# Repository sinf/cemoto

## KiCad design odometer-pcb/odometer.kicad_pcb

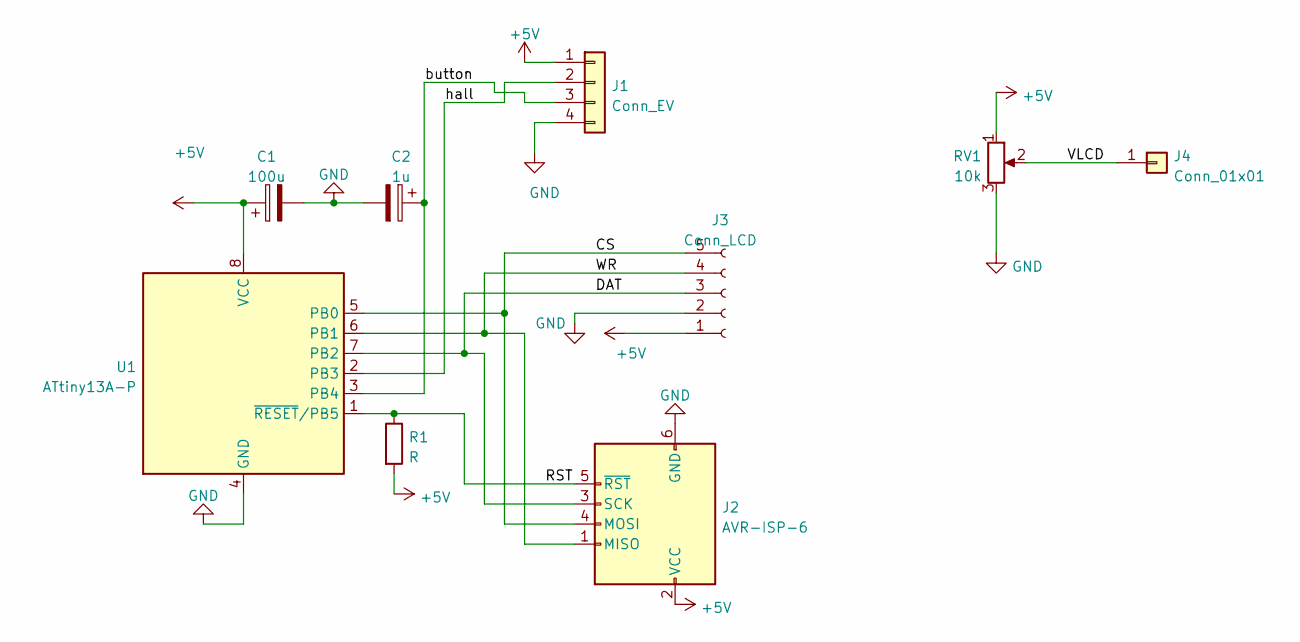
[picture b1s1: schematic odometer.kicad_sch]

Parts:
C1: 100u; CP_Radial_D8.0mm_P5.00mm
C2: 1u; CP_EIA-3216-12_Kemet-S
J1: Conn_EV; PinHeader_1x04_P2.54mm_Vertical
J2: AVR-ISP-6; PinHeader_2x03_P2.54mm_Vertical_SMD
J3: Conn_LCD; PinHeader_1x05_P2.54mm_Vertical
J4: Conn_01x01; PinHeader_1x01_P2.54mm_Vertical
R1: R; R_1206_3216Metric_Pad1.30x1.75mm_HandSolder
RV1: 10k; Potentiometer_ACP_CA9-H5_Horizontal
U1: ATtiny13A-P; DIP-8_W7.62mm

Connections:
+5V: C1.1, J1.1, J2.2 (VCC), J3.1, R1.2, RV1.1, U1.8 (VCC)
/CS: J2.4 (MOSI), J3.5, U1.5 (PB0)
/DAT: J2.3 (SCK), J3.3, U1.7 (PB2)
/RST: J2.5 (~RST), R1.1, U1.1 (~RESET/PB5)
/VLCD: J4.1, RV1.2
/WR: J2.1 (MISO), J3.4, U1.6 (PB1)
/button: C2.1, J1.3, U1.3 (PB4)
/hall: J1.2, U1.2 (PB3)
GND: C1.2, C2.2, J1.4, J2.6 (GND), J3.2, RV1.3, U1.4 (GND)

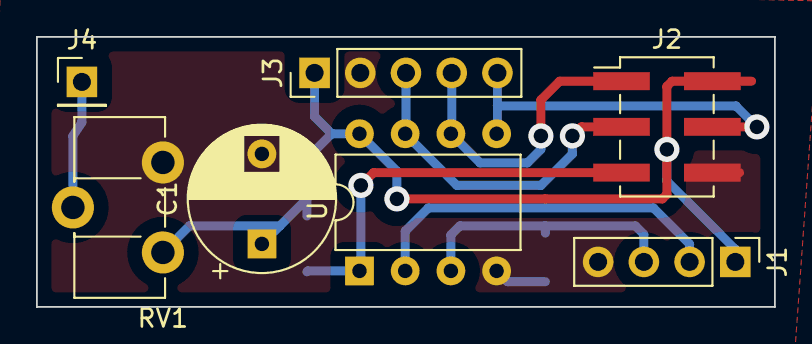
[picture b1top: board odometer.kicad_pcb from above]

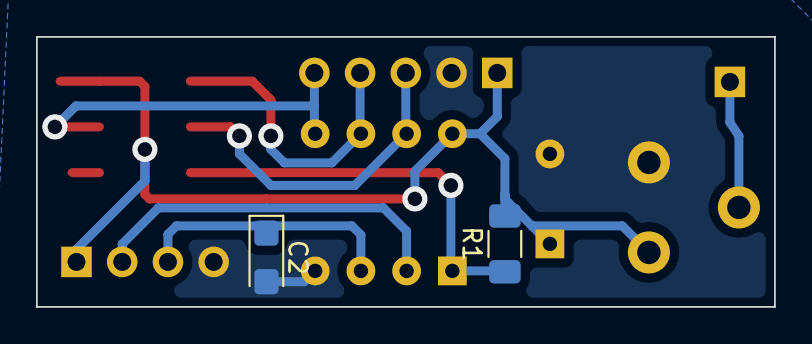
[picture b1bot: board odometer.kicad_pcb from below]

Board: 2 copper layers, 41.0 x 15.0 mm, 9 parts (2 on the bottom side), 9 nets.

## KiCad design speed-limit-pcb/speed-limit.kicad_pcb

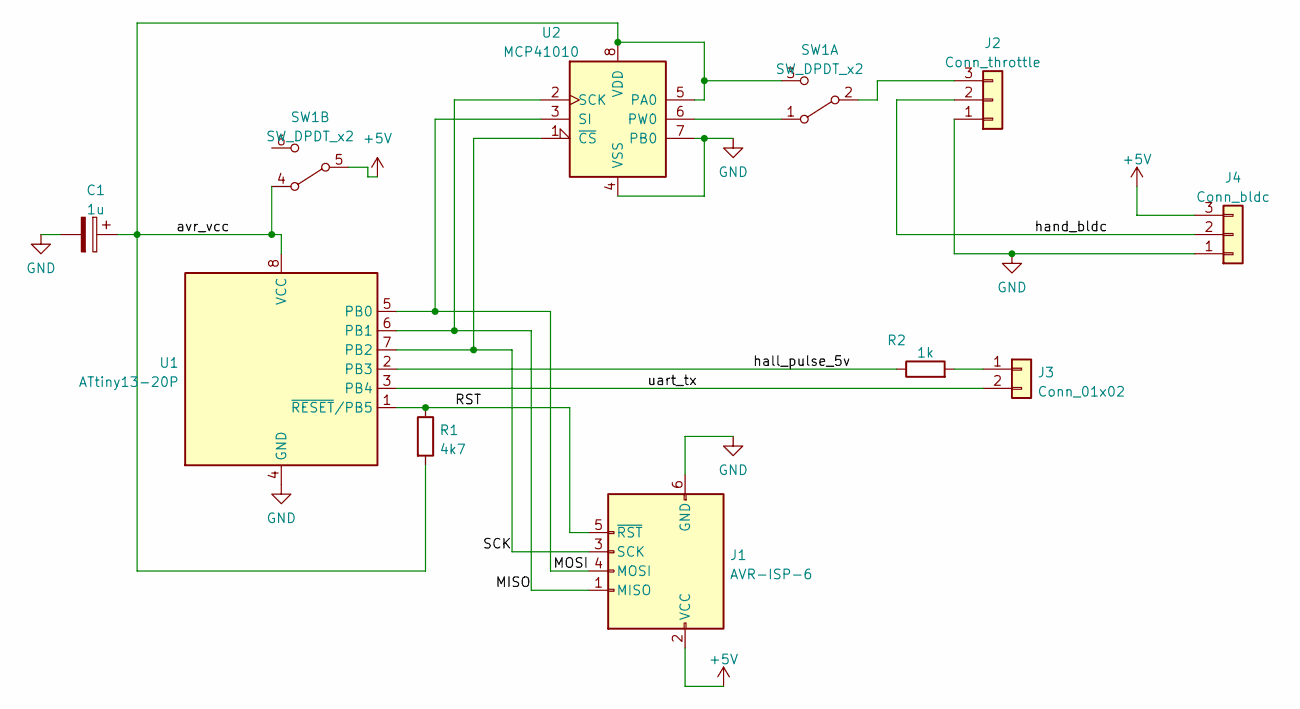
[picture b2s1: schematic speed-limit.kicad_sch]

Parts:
C1: 1u; CP_Radial_D8.0mm_P5.00mm
J1: AVR-ISP-6; SW_DIP_SPSTx03_Slide_9.78x9.8mm_W8.61mm_P2.54mm
J2: Conn_throttle; SolderWire-1.5sqmm_1x03_P6mm_D1.7mm_OD3mm
J3: Conn_01x02; SolderWire-1.5sqmm_1x02_P6mm_D1.7mm_OD3mm
J4: Conn_bldc; SolderWire-1.5sqmm_1x03_P6mm_D1.7mm_OD3mm
R1: 4k7; R_1210_3225Metric_Pad1.30x2.65mm_HandSolder
R2: 1k; R_1210_3225Metric_Pad1.30x2.65mm_HandSolder
SW1: SW_DPDT_x2; SolderWire-1.5sqmm_1x06_P6mm_D1.7mm_OD3mm
U1: ATtiny13-20P; DIP-8_W7.62mm_Socket_LongPads
U2: MCP41010; DIP-8_W7.62mm_Socket_LongPads

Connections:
+5V: J1.2 (VCC), J4.3, SW1.5 (B)
/MISO: J1.1 (MISO), U1.6 (PB1), U2.2 (SCK)
/MOSI: J1.4 (MOSI), U1.5 (PB0), U2.3 (SI)
/RST: J1.5 (~RST), R1.1, U1.1 (~RESET/PB5)
/SCK: J1.3 (SCK), U1.7 (PB2), U2.1 (~CS)
/avr_vcc: C1.1, R1.2, SW1.3 (C), SW1.4 (A), U1.8 (VCC), U2.5 (PA0), U2.8 (VDD)
/hall_pulse_5v: R2.1, U1.2 (PB3)
/hand_bldc: J2.2, J4.2
/uart_tx: J3.2, U1.3 (PB4)
GND: C1.2, J1.6 (GND), J2.1, J4.1, U1.4 (GND), U2.4 (VSS), U2.7 (PB0)
unnamed: J2.3, SW1.2 (B)
unnamed: J3.1, R2.2
unnamed: SW1.1 (A), U2.6 (PW0)

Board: 2 copper layers, 10 parts (0 on the bottom side), 13 nets, no tracks yet.

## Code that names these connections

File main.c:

#ifndef F_CPU
#define F_CPU 9600000UL
#endif

#include <stdint.h>
#include <stdlib.h>
#include <string.h>
#include <math.h>
#include <avr/io.h>
#include <avr/interrupt.h>
#include <util/delay.h>
#include <util/delay_basic.h>

// digital potentiometer pins
// max spi freq = 10 MHz
#define SDI (1u<<0)
#define SCK (1u<<1)
#define CS (1u<<2)
#define spi_delay() _delay_loop_1(10)
#define spi_delay2() _delay_loop_1(30)

#define HALL (1u<<3)
#define LED (1u<<4)

#include "speed.c"

int16_t wiper_pos = WIPER_MAX;
volatile pulse_t pulse_counter = 0; // should increment at rate < 1000 Hz
volatile rtc_t rtc_counter = 0;

ISR(TIM0_OVF_vect) {
	rtc_counter += 1;
}

ISR(PCINT0_vect) {
	if (pulse_counter != PULSE_MAX)
		pulse_counter += 1;
}

#if 0
#define boot_anim()
#else
void boot_anim() {
	for(int i=0; i<5; ++i) {
		PORTB ^= LED;
		_delay_ms(100);
	}
	PORTB = PORTB & (~LED);
}
#endif

#define CMD_8(addr,cmd,data) ((addr)<<4 | (cmd)<<2 & 12 | (data) & 3)
#define CMD_16(addr,cmd,data) ((uint16_t) CMD_8((addr),(cmd),(uint16_t)(data) >> 8) << 8 | (uint8_t)(data) & 0xFFu)

// cmd bits
#define CMD_WRITE 0
#define CMD_INCR 1
#define CMD_DECR 2
#define CMD_READ 3

// addresses
#define WIPER0 0
#define WIPER1 1
#define TCON 2
#define STATUS 5

void spi_send(uint16_t data, uint8_t bits)
{
	data <<= 16 - bits;
	PORTB &= ~CS;
	spi_delay2();

	for(uint8_t i=0; i<bits; ++i) {

		uint8_t data_bit = data << i >> 15;

		PORTB = PORTB & ~(SCK | SDI);
		PORTB |= data_bit;
		spi_delay();

		PORTB |= SCK;
		spi_delay();
	}

	spi_delay2();
	PORTB |= CS;
}

void inc_wiper(int8_t delta) {
	spi_send(CMD_8(WIPER0, delta > 0 ? CMD_INCR : CMD_DECR, 0), 8);
}

void set_wiper(int16_t value) {
	if (value < 0) { value = 0; }
	if (value > WIPER_MAX) { value = WIPER_MAX; }
	wiper_pos = value;

#if 1
	if (value > 0) {
		PORTB |= LED;
	} else {
		PORTB &= ~LED;
	}
#endif

	spi_send(CMD_16(TCON, CMD_WRITE, 0x1FF), 16); // just in case a random bit flip corrupts TCON
	spi_send(CMD_16(WIPER0, CMD_WRITE, value), 16);
}

#if 0
void test_wiper() {
	int16_t w = 0;
	int16_t d = 1;
	for(;;) {
		set_wiper(w);
		w += d;
		if (w == 0 || w == WIPER_MAX) {
			d = -d;
		}
	}
}
#endif

int main(void)
{
	/*
	 * PB0: data of digi pot (SDI/SDO/SI)
	 * PB1: SCK of digi pot
	 * PB2: CS of digi pot
	 * PB3: hall sensor
	 * PB4: output LED
	 * DDRB 1-bits mean outputs
	 * PORTB 1-bits for inputs enables pull up
	 */
	DDRB = LED | SCK | CS | SDI;
	PORTB = CS | HALL; // pull ups
	
	/* setup timer interrupt */
	TCCR0A = 0; // dont toggle hardware pin, normal mode
	TCCR0B = 1<<CS00 | 1<<CS01; // prescaler = 64
	TIMSK0 = 1<<TOIE0; // enable overflow interrupt for timer 0

	/* setup pin change interrupt */
	PCMSK = 1<<PCINT3;
	GIMSK = 1<<PCIE;

	boot_anim();
	//PORTB |= LED;
	
	set_wiper(wiper_pos);

	rtc_t rtc_acc[N_ACC] = {0};
	pulse_t pulse_acc[N_ACC] = {0};
	uint8_t i_acc = 0;

	sei();

	for(;;) {
		rtc_t rtc_copy;
		pulse_t pulse_copy;

		while (rtc_counter < TICK_INTERVAL) { }
		cli();
		rtc_copy = rtc_counter;
		pulse_copy = pulse_counter;
		rtc_counter = 0;
		pulse_counter = 0;
		sei();

		rtc_acc[i_acc] = rtc_copy;
		pulse_acc[i_acc] = pulse_copy;
		if (++i_acc == N_ACC) {
			i_acc = 0;
		}

		uint16_t t=0, p=0;
		for(int j=0; j<N_ACC; ++j) {
			t += rtc_acc[j];
			p += pulse_acc[j];
		}

		//t <<= 1; // adjust because counted all pulses twice
		p >>= 1;

		int16_t w = calc_speed(p, t);
		set_wiper(w);
	}

	return 0;
}

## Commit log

2021-04-25 LICENSE: nimen muutos
2021-04-25 gitignore
2021-04-25 avr-libc example code
2021-04-25 add pictures
2021-04-25 arduino example
2021-04-25 add video
2021-04-25 fix link markdown
2021-04-25 add gif
2022-09-22 digital pot working
2022-09-22 digital pot demo; bugs fixed
2022-09-26 correct speed calculation, pot control, unit tests
2022-09-28 delete
2022-09-28 initial working demo thingy
2022-09-28 first version
2022-09-30 .gitignore
2022-09-30 speed-limit-fw
2022-09-30 speed limit pcb
2022-09-30 odometer pcb
2022-09-30 rename
2022-09-30 LICENCE
2022-09-30 schematic-12v
2022-09-30 schematic-12v update
2023-06-17 update kicad version, add charger relay
